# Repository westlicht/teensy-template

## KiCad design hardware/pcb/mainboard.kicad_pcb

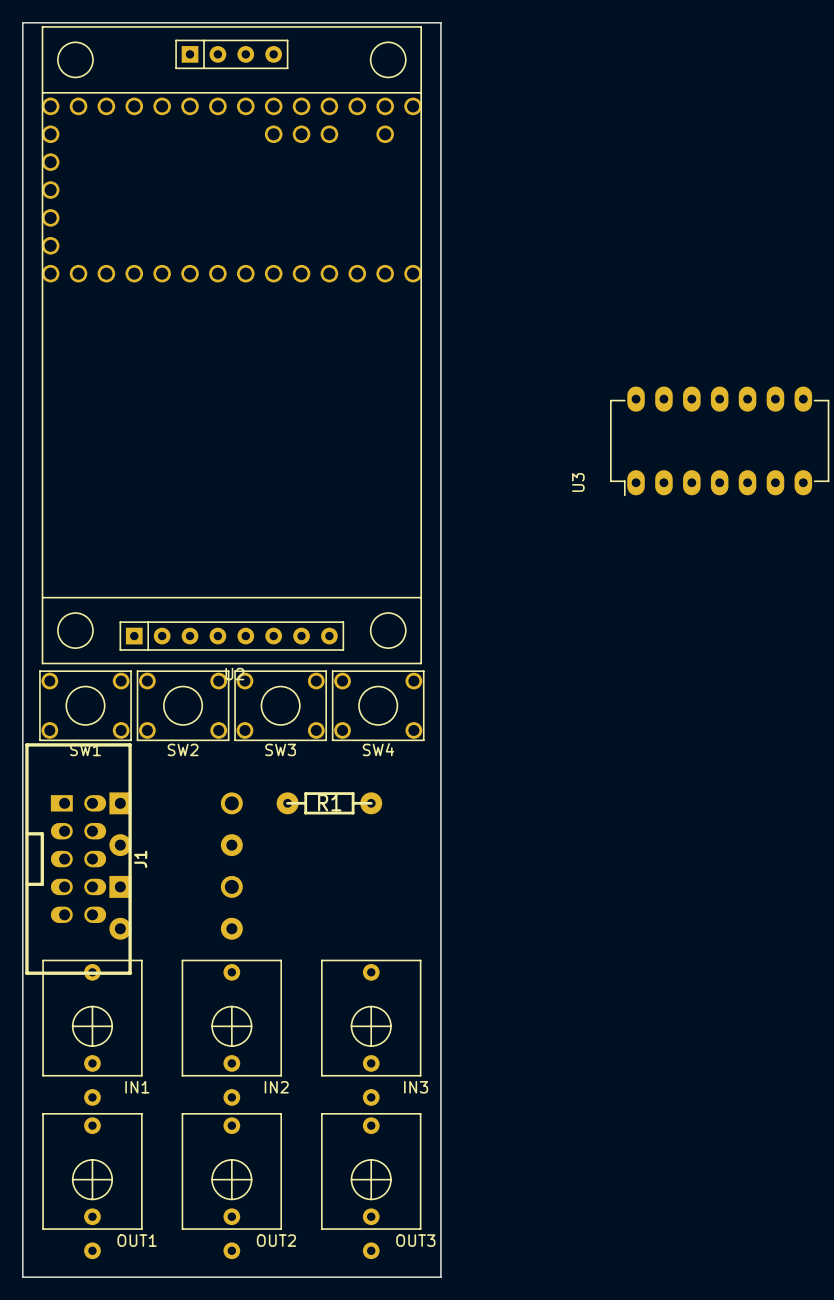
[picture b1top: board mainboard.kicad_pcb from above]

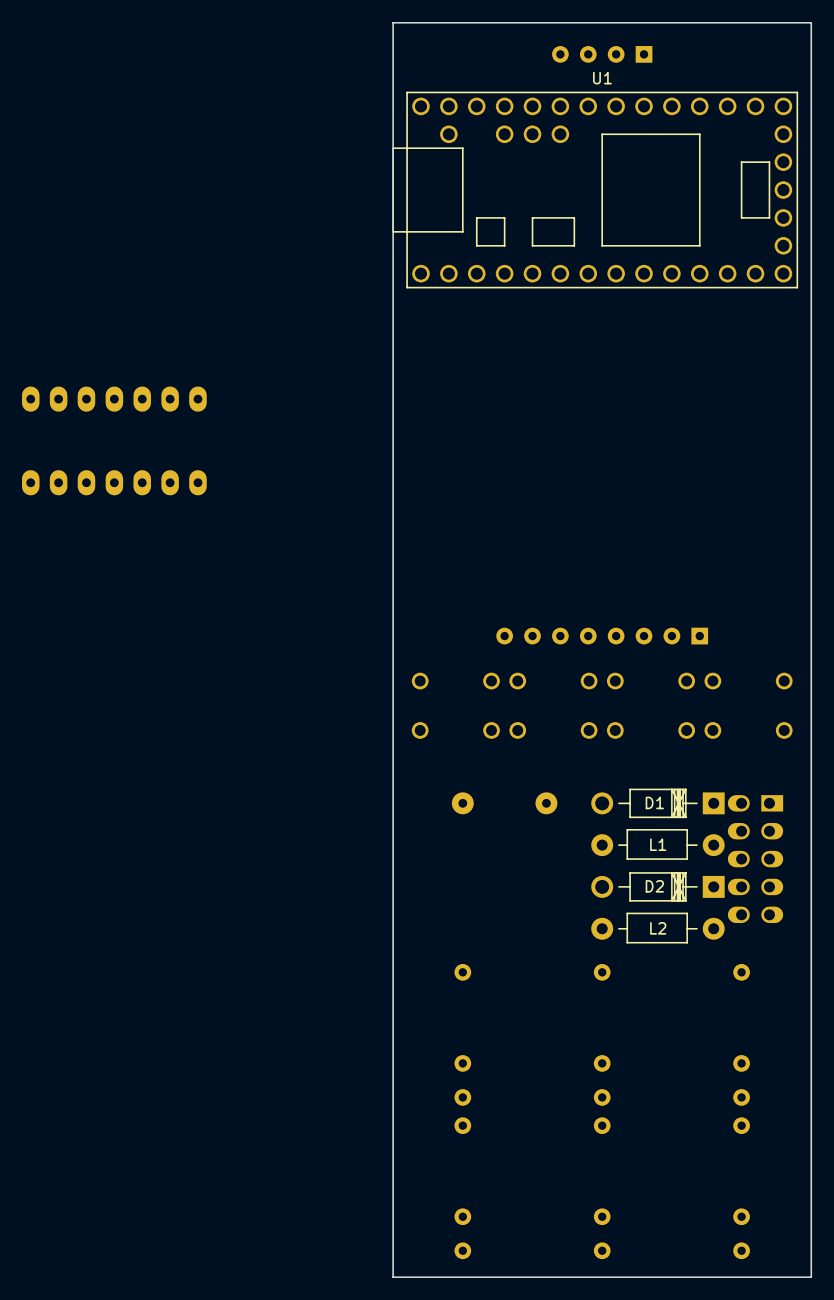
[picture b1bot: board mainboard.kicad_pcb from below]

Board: 2 copper layers, 38.1 x 114.3 mm, 19 parts (5 on the bottom side), 14 nets, no tracks yet.

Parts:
D1, D2: 1N4001; Diode_DO-41_SOD81_Horizontal_RM10
IN1, IN2, IN3: PJ301M-12
J1: EURO_PWR_2x5; vasch_strip_5x2
L1, L2: BL01RN1A; Choke_Horizontal_RM10mm
OUT1, OUT2, OUT3: PJ301M-12
R1: R; RC03
SW1, SW2, SW3, SW4: TL1105SPF250Q
U1: Teensy3.2; Teensy3.x_LC
U2: TFT01-1.8SP
U3: TL074; DIP-14_W7.62mm_LongPads

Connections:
+12V_INLET: D1.1, J1.1, J1.2, L1.2
-12V_INLET: D2.2, J1.9, J1.10, L2.2
GND: D1.2, D2.1, J1.3, J1.4, J1.5, J1.6, J1.7, J1.8, SW1.1, SW1.2, SW2.1, SW2.2, SW3.1, SW3.2, SW4.1, SW4.2, U2.2
IN_A: IN1.3, OUT1.3
IN_B: IN2.3, OUT2.3
IN_T: IN3.3, OUT3.3
MISO: U1.14, U2.11
MOSI: U1.13, U2.10
unnamed: IN1.1, IN2.1, IN3.1, OUT1.1, OUT2.1, OUT3.1
SCK: U1.20, U2.7, U2.12
SW_1: SW1.3, U1.7
SW_2: SW2.3, U1.6
SW_3: SW3.3, U1.5
SW_4: SW4.3, U1.4

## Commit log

2016-08-04 moved tools to tools-linux
2016-08-04 updated teensy3 library from teensyduino 1.29
2016-08-04 added osx tools from teensyduino 1.29
2016-08-04 added libraries
2016-08-04 updated to use teensy 3.1/3.2
2016-08-04 automatically use osx or linux tools
2016-08-04 added spi library
2016-08-05 updated linux tools with latest versions from teensyduino 1.29
2018-09-29 gitignored .DS_Store
2018-09-29 initial import of scope application
2018-09-29 update submodules
2018-09-29 updated Makefile
2018-09-29 initial import of hardware design files
